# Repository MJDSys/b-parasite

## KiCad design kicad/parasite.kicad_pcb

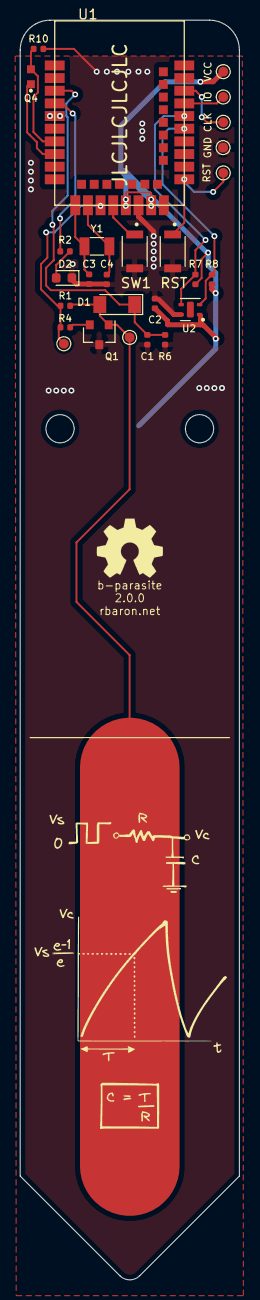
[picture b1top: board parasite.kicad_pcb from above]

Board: 2 copper layers, 22.0 x 126.4 mm, 28 parts (1 on the bottom side), 18 nets.

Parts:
BT1: Battery_Cell; BatteryHolder_Keystone_3002_1x2032
C1: 1n; C_0402_1005Metric
C2: 100n; C_0402_1005Metric
C3, C4: 12p; C_0402_1005Metric
D1: LL4148; D_MiniMELF
D2: LED; LED_0603_1608Metric
Q1: 2N3906; SOT-23
Q4: Q_Photo_NPN; TR8
R1, R4, R7, R8: 10k; R_0402_1005Metric
R2: 1k; R_0402_1005Metric
R6: 1M; R_0402_1005Metric
R10: 470; R_0402_1005Metric
RST: B3U-1000P; SW_B3U-1000P
SW1: B3U-1000P; SW_B3U-1000P
TP1: IO; TestPoint_Pad_D1.0mm
TP2: CLK; TestPoint_Pad_D1.0mm
TP3: GND; TestPoint_Pad_D1.0mm
TP4: RST; TestPoint_Pad_D1.0mm
TP5: CPARA; TestPoint_Pad_D1.0mm
TP6: PWM; TestPoint_Pad_D1.0mm
TP7: VCC; TestPoint_Pad_D1.0mm
U1: E73-2G4M08S1C
U2: SHTC3; Sensirion_DFN-4-1EP_2x2mm_P1mm_EP0.7x1.6mm
Y1: 32.768kHz; Crystal_SMD_3215-2Pin_3.2x1.5mm

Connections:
+3V0: BT1.1 (+), C2.1, R7.2, R8.1, TP7.1, U1.19 (VDD), U1.23 (VDDH), U2.1 (VDD)
BTN1: SW1.1, U1.17 (P1.09)
CPARA: D1.2 (A), Q1.1 (E), R1.2, TP5.1
GND: BT1.2 (-), C1.2, C2.2, C3.1, C4.2, D2.1 (K), Q1.3 (C), R6.2, R10.1, RST.2, SW1.2, TP3.1, U1.5 (GND@1), U1.21 (GND@2), U2.4 (VSS)
LED: R2.2, U1.4 (P0.28/AIN4)
unnamed: C3.2, U1.11 (P0.00/XL1), Y1.2
unnamed: C4.1, U1.13 (P0.01/XL2), Y1.1
unnamed: D2.2 (A), R2.1
unnamed: Q1.2 (B), R4.1
PHOTO_OUT: Q4.2 (E), R10.2, U1.7 (P0.02/AIN0)
PHOTO_V: Q4.1 (C), U1.8 (P0.29/AIN5)
PWM: R1.1, R4.2, TP6.1, U1.15 (P0.05/AIN3)
RST: RST.1, TP4.1, U1.26 (P0.18/RESET)
SCL: R8.2, U1.33 (P0.13), U2.2 (SCL)
SDA: R7.1, U1.35 (P0.24), U2.3 (SDA)
SENS_OUT: C1.1, D1.1 (K), R6.1, U1.3 (P0.03/AIN1)
SWDCLK: TP2.1, U1.39 (SWDCLK)
SWDIO: TP1.1, U1.37 (SWDIO)

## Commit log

2022-11-06 Some initial hardware changes for the 2.0.0 revision
    - Simplified the fast discharge circuit to use a single PNP BJT instead
    of two NPN BJTs
    - Swapped nRF52 module's footprint for one with larger pads
    - Added a user button tied to P0.12 (same as Button 2 from [nrf52840_dk](https://infocenter.nordicsemi.com/index.jsp?topic=%2Fug_nrf52840_dk%2FUG%2Fdk%2Fhw_buttons_leds.html))
    - Added a reset switch
    These are only schematic changes - PCB layout is stale and needs to be
2022-11-06 New PWM testpoint and added LCSC part # for the E73 module
2022-11-07 Initial routing complete
2022-11-08 Adds sketch of RC circuit in silkscreen
2022-11-23 Slightly better routing
